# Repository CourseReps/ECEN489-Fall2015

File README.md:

# Data Acquisition &amp; Embedded Systems

## Description

The goal of this multidisciplinary project-based laboratory course is to provide instruction on data acquisition, system-level integration and design through a range of hands-on activities that complement the traditional classroom experience.
This includes circuit prototyping, PCB fabrication, microcontrollers and C++ programming, networking, and data visualization.
The main focus is on modular application development, algorithms, information management, control and actuation.
In addition, emphasis is put on team work, presentation skills, time management, creativity and innovation.

## Objectives

1. Enhance engineering education by facilitating learning through engineering projects.
2. Review the basics of circuit building, programming concepts, computer-aided design tools, the fundamentals of microcontrollers.
3. Foster leadership and team work, with division of labor, complementary tasks, discussion and integration.
4. Develop the ability to bridge theoretical concepts and practical tasks.
5. Master elements of experiential learning such as abstract conceptualization, active experimentation, concrete experience, reflective observation.
6. Improve transferable engineering skills and the ability to integrate different concepts.
7. Develop confidence and leadership.
8. Promote creativity and critical thinking.
9. Refine presentation skills and the ability to conduct and manage projects.

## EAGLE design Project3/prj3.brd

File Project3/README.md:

# Project 3

# Team Assignment

## [Team 1](https://github.com/CourseReps/ECEN489-Fall2015/wiki/project3-team1)

* Kartic Bhargav
* Thomas Branyon
* Henry Xiangdong Yu
* Kan Zheng

## [Team 2](https://github.com/CourseReps/ECEN489-Fall2015/wiki/project3-team2)

* Anthony Ramirez
* Keaton Brown
* Travis Taghavi
* Austin Taghavi
* Blade Roybal (Free Agent)

## [Team 3](https://github.com/CourseReps/ECEN489-Fall2015/wiki/project3-team3)

* Kaimen Walters
* Steven Jinpeng You
* Hai Li
* Pranay Eedara

## [Team 4](https://github.com/CourseReps/ECEN489-Fall2015/wiki/project3-team4)

* Udaya Bhaskar Kothapalli
* Abhay Anand
* Cooper Rehn
* Seungwon Yoon

# Simulation/Model Testing
In order to verify our models and algorithms, all the teams will test their models using the same values/input files.
##Problem 1
For the single-bucket volume estimation problem, we define the model to have the following parameters (equivalent to a standart 500ml beaker):
* Bucket diameter - 8cm
* Bucket height - 12cm
* Hole/leak diameter - 5mm
* Max flowrate - 3.5 L/min
    - Flowrate is assumed to be linear with PWM value between 0 and 255. i.e., PWM of 255 will yield a flowrate of 3.5L/min, and a PWM of 0 will yield a flow of 0L/min

Our input to the simulation will just be these four values, plus two more - a setpoint, and a height "jump" that occurs when the object is dropped in. To start, we will use the following test cases:
* Setpoint = 6cm, jump = 1cm
* Setpoint = 3cm, jump = 2cm

The input file will be all 6 values comma-separated. Example:

File 1:

    8, 12, 5, 3.5, 6, 1
    
File 2:

    8, 12, 5, 3.5, 3, 2

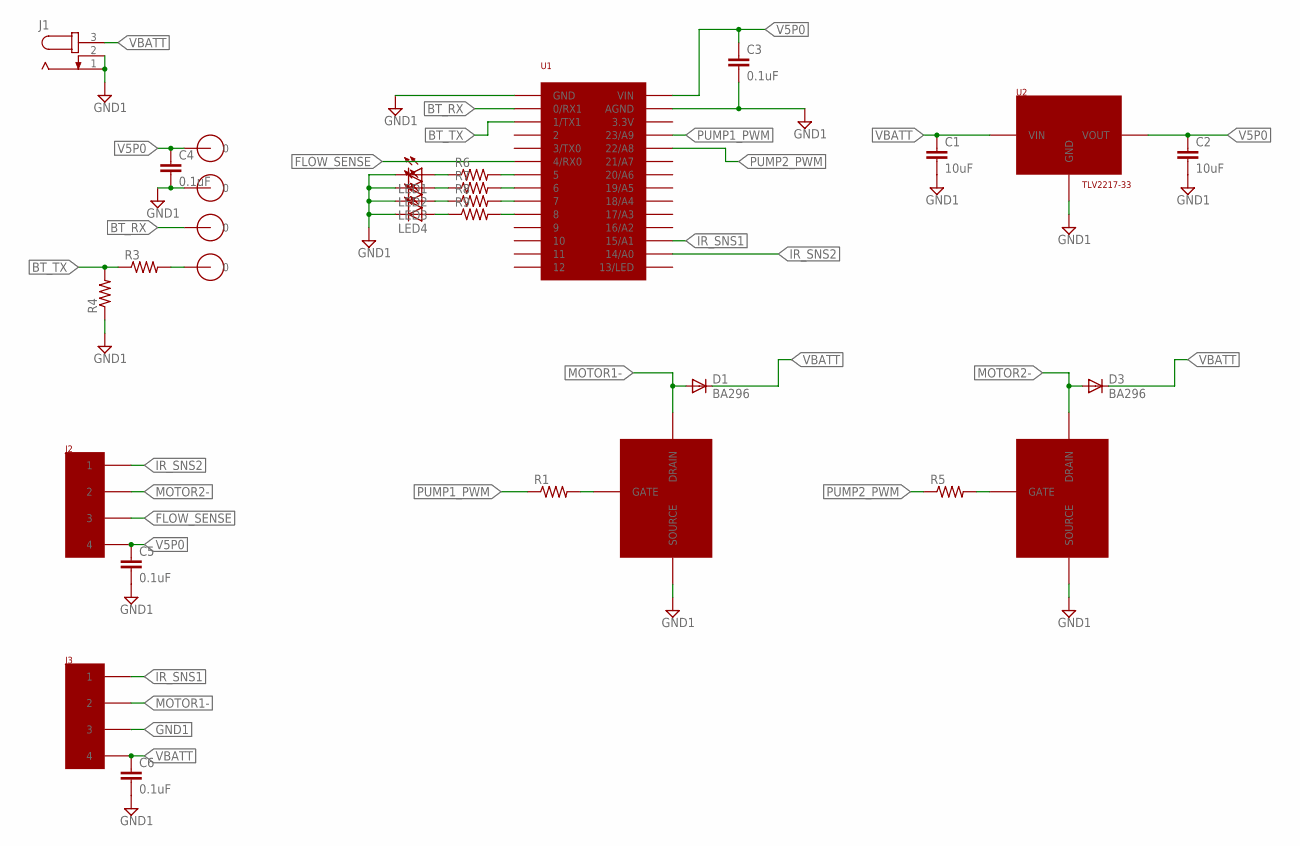
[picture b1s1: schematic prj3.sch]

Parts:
C1, C2: 10uF; C2.5-3
C3, C4, C5, C6: 0.1uF; C2.5-3
D1, D3: BA296; P2-15
J1: JACK-PLUG0; SPC4077
J2, J3: 1776119-4; 4P_SCREW_TERMINAL
J7, J8, J9, J10: 35MIL_HOLE
LED1, LED2, LED3, LED4: LED_ELD260; LED_LD260
R1, R3, R4, R5, R6, R7, R8, R9: R-US_0207/10; 0207/10
U1: TEENSY
U2: TLV2217-33; TO-220
U$2, U$3: NFET; TO-220

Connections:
BT_RX: J9.P$1, U1.P$2 (0/RX1)
BT_TX: R3.1, R4.2, U1.P$3 (1/TX1)
FLOW_SENSE: J2.P$3 (3), U1.P$6 (4/RX0)
GND1: C1.2, C2.2, C3.2, C4.2, C5.2, C6.2, J1.1, J1.2, J3.P$3 (3), J8.P$1, LED1.K (C), LED2.K (C), LED3.K (C), LED4.K (C), R4.1, U1.P$1 (GND), U1.P$32 (AGND), U2.2 (GND), U$2.3 (SOURCE), U$3.3 (SOURCE)
IR_SNS1: J3.P$1 (1), U1.P$22 (15/A1)
IR_SNS2: J2.P$1 (1), U1.P$21 (14/A0)
MOTOR1-: D1.A, J3.P$2 (2), U$2.2 (DRAIN)
MOTOR2-: D3.A, J2.P$2 (2), U$3.2 (DRAIN)
unnamed: R1.2, U$2.1 (GATE)
unnamed: R5.2, U$3.1 (GATE)
unnamed: R6.2, U1.P$7 (5)
unnamed: J10.P$1, R3.2
unnamed: R7.2, U1.P$8 (6)
unnamed: R8.2, U1.P$9 (7)
unnamed: R9.2, U1.P$10 (8)
unnamed: LED1.A, R6.1
unnamed: LED2.A, R7.1
unnamed: LED3.A, R8.1
unnamed: LED4.A, R9.1
PUMP1_PWM: R1.1, U1.P$30 (23/A9)
PUMP2_PWM: R5.1, U1.P$29 (22/A8)
V5P0: C2.1, C3.1, C4.1, C5.1, J2.P$4 (4), J7.P$1, U1.P$33 (VIN), U2.3 (VOUT)
VBATT: C1.1, C6.1, D1.C, D3.C, J1.3, J3.P$4 (4), U2.1 (VIN)

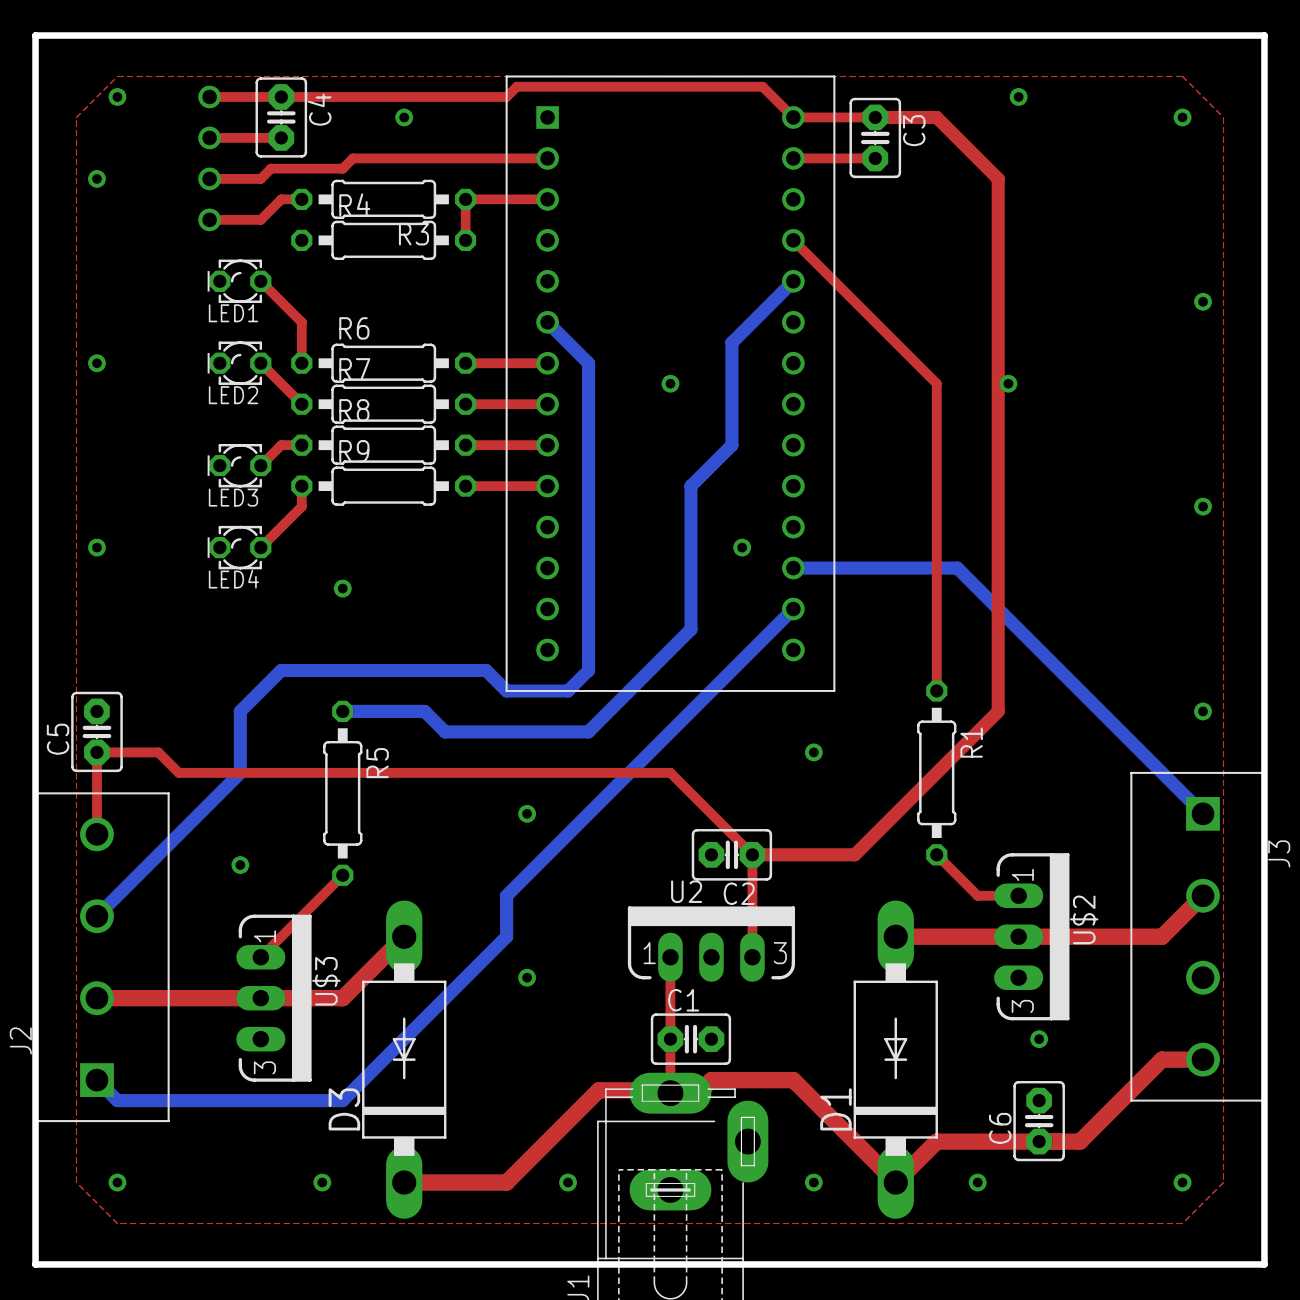
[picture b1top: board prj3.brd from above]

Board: 2 copper layers, 76.2 x 76.2 mm, 31 parts (0 on the bottom side), 23 nets.

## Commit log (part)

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2015-09-16 minor change
2015-09-16 Adding files for KiCad tutorial
2015-09-16 Adding Assignment 2 Programming Challenge
2015-09-16 Add optout3
2015-09-16 adding optout 3
2015-09-16 Adding Assignment 3
    Broken
2015-09-16 chaning port for server
2015-09-16 Updating Assignment 3
    Working now
2015-09-16 Added option to choose port in client
2015-09-16 Minor change to 3optout client
2015-09-16 Fixed format to ensure jpg rather than png
2015-09-16 Minor change in client
2015-09-16 cmake assignment3
2015-09-16 Deleting vestigial files.
2015-09-16 Assignment 4.
2015-09-17 Adding KiCad tutorial files
2015-09-17 Updating pictures
2015-09-17 3optout
2015-09-17 change name
2015-09-17 added tutorial folder :
2015-09-17 Updating 1optout
2015-09-18 Deleting .gitignore
2015-09-18 Adding 3optout
2015-09-18 Rename README to README.md
2015-09-18 Assignment 4
2015-09-18 cleanup
2015-09-18 optout3
2015-09-18 optout3 library files
2015-09-18 Rename arduinocode to arduinocode.ino
2015-09-18 optout3 readme files
2015-09-18 example of sqilte in c
2015-09-18 add the cmakelist
2015-09-20 assignment4
2015-09-20 4optout
2015-09-21 Adding server and client files
2015-09-21 Changing directory and adding CMakeLists
2015-09-21 Editing server so that it doesn't leave db open
2015-09-21 minor update
2015-09-21 Updating README.md
2015-09-21 final
2015-09-21 small deletions
2015-09-21 deleting unwanted files
2015-09-21 optout4 broadcast and server files
2015-09-21 Adding optout 4
2015-09-21 Adding port number as command line arg
2015-09-21 add optout4
2015-09-21 remove idea files
2015-09-21 Adding Assignment 4
2015-09-21 Assignment 5.
2015-09-22 Assignment 5
2015-09-23 update assignments
2015-09-23 Updating server.cpp
2015-09-24 assignment5
2015-09-24 add 4optout
2015-09-24 aaaa
2015-09-24 delete
2015-09-25 assn2 update
2015-09-25 optout4 updates
2015-09-25 Sample codes for Bluetooth tutorial
2015-09-25 Added assignment 5
2015-09-25 Adding Assignment 5 files
2015-09-25 no message
2015-09-25 Adding Assignment 5
2015-09-25 Updating Assignment 5
2015-09-25 asdf
2015-09-25 adding quickfire
2015-09-29 Adding readme
2015-09-29 Edited client.cpp
2015-09-29 assignment6
2015-09-30 Assignment 6
2015-09-30 initial commit of 6optout
2015-09-30 6optout
2015-09-30 Adding 6optout
2015-09-30 Editing README.md
2015-09-30 Adding 6optout files
2015-09-30 Add readme for 6optout
2015-09-30 added assignment 6
2015-09-30 Fixed Server.cpp bug
2015-09-30 optout6 files
2015-09-30 Changed to non-privileged port on client
2015-09-30 add optOut6
2015-09-30 Updated README for 6optout
2015-09-30 optout6 modification
2015-09-30 Adding Assignment 6
2015-09-30 update tutorials
2015-09-30 Assignment6 revision
2015-09-30 removing junk
2015-09-30 optout6 code update
2015-10-02 Corrected 6optout sources
2015-10-03 modify 6optout
2015-10-05 Fixed quickfire 3 files
2015-10-05 Adding Optout4
2015-10-05 test2foroptout7
2015-10-05 Adding quickfire and 7optout
2015-10-05 commiting 6optout and quickfire
2015-10-05 7optout
2015-10-05 Adding teams for Project 1.
2015-10-05 Adding graders.
2015-10-06 add 7optout
2015-10-06 Various updated files - merging
2015-10-06 Initial commit of 7optout - unstable
2015-10-06 Updated 7optout files
2015-10-07 Adding optout6
2015-10-07 optout6 edit teensy code
2015-10-07 optout7
2015-10-07 quickfire
2015-10-07 making a tiny change to ui
2015-10-07 Graders.
2015-10-07 Updating list of students in graders.cpp.
2015-10-07 optout7 threading
2015-10-08 optout7 threading update
2015-10-08 adding motor control tutorial sketch
2015-10-08 modified 7optout
2015-10-09 Adding client for Project1
2015-10-11 modify 7optout
2015-10-11 Adding PWM and Sensor Measurement
2015-10-12 small changes
2015-10-12 Updating client
2015-10-12 1project bluetoothbasic
2015-10-13 qtplot
2015-10-13 1project bluetooth server
2015-10-14 Adding Project1 Files
2015-10-14 Adding 7optout
2015-10-14 Adding project 1 sketch
2015-10-14 Project 1 code
2015-10-14 Adding arduino sensor reading code
2015-10-14 add project1
2015-10-14 plots for 1project
2015-10-14 Updating Proj 1
2015-10-15 Added new visualisation QT Creator project
2015-10-16 adding teensy code
2015-10-16 Adding Project1Server
2015-10-16 Final project 1 teensy sketch
2015-10-16 adding server
2015-10-16 updating server
2015-10-16 Project1 NUC code
2015-10-16 update server
2015-10-16 updating
2015-10-16 adding server and client and updating vis
2015-10-16 Updating Project1Server
2015-10-16 Updating visuals
2015-10-16 updating arduino code
2015-10-16 1project BTclient server working
2015-10-19 Adding teams for project 2.
2015-10-21 Add Schematic Project1
2015-10-21 Add CustomComponents
2015-10-23 adding arduino files for PID
2015-10-23 updating files
2015-10-23 adding proj2 temp sketch
2015-10-25 add project1 programs
2015-10-25 rm team2 directory in project1
2015-10-26 adding arduino PID code
2015-10-26 Adding Project2 folder
2015-10-28 Arduino code updated
2015-10-30 PID working code
2015-11-02 Adding proj 2 screenshots
2015-11-03 Adding teensy bluetooth prj2
2015-11-03 updating project 2 teensy sketch for BT
2015-11-04 2project Qt console
2015-11-04 2project Teensy code
2015-11-04 2project modified Qt
2015-11-04 2project teensy code updated
2015-11-04 Create project2
2015-11-04 updating plotter
2015-11-04 Adding server for P2
2015-11-04 modifying server
2015-11-04 updated arduino code
2015-11-04 project 2 files
2015-11-04 add images
2015-11-04 updated teensy sketch
2015-11-04 adding some debugging to server
2015-11-04 adding QT and Arduno
2015-11-06 Final Project 2
2015-11-06 deleting garbage
2015-11-06 adding board image
2015-11-06 updating server for bt reading
2015-11-06 add image
2015-11-09 solidworks
2015-11-09 Add Screenshots
2015-11-09 adding qt image
2015-11-13 File Clean up
2015-11-13 Project 3 schem
2015-11-13 pcb for project2
2015-11-13 Adding BOM
    v1
2015-11-13 Project 3 PCB
2015-11-15 Finished project 3 board and BOM
2015-11-16 Adding project 3 PCB files
2015-11-16 Add PCB Screenshot
2015-11-16 Moving project 3 PCB files to Team 4 folder
2015-11-16 Adding prelimiary Python code for the model
2015-11-16 add libraries used
2015-11-16 clean up folder
2015-11-16 Add PCB Screenshots
2015-11-16 arduino code for team4
2015-11-17 updates in 2project
2015-11-17 3project Qt model
2015-11-17 simulator demo
2015-11-18 modify simulator
2015-11-18 Adding Project3 Wiki images
2015-11-18 part1upload
2015-11-18 Update images in Project3
2015-11-18 update: adding label
2015-11-18 Adding PCB screens and block diagram
2015-11-18 3project image1
2015-11-18 singlt tank image
2015-11-18 remove image
2015-11-18 Adding project3 files
2015-11-18 Adding model stuff
2015-11-18 single tank image modified
2015-11-18 Adding images
2015-11-18 coupled tank image
2015-11-20 Adding images for project 3 wiki
2015-11-20 Adding Flow Rate calibration
    Measures flow rate from hall sensor and time taken to calibrate using a
    1L bottle. Updated constant can be used improve accuracy
2015-11-23 Update flowRate
    Updated to prevent max pump output at beginning
2015-11-23 Update flowRate
    Try 3
2015-11-30 modified for object volume calc
2015-11-30 Full model without visualization
2015-11-30 adding database
2015-11-30 update simulator
2015-11-30 committing database changes intermittantly, so that real time plotting is possible
2015-12-02 Project3 Server BT comms
2015-12-02 Adding ARduino code
2015-12-04 Updating proj 3 files
2015-12-04 updated project 3
2015-12-04 Adding teensy code (unstable). Base is Abhay Anand - Project 2.
2015-12-04 Adding pump cablibration routine
2015-12-06 Adding pictures for documentation
2015-12-06 fixing images
2015-12-06 add project 3
2015-12-07 modify project3
2015-12-07 Adding project 3 calibrations
2015-12-07 Adding newest teensy code. Object detection for tank 1 and comms for both tanks working. Volume calculation is off by a factor of 5-10.
2015-12-07 Adding PId code
2015-12-07 Adding PID2 code
2015-12-08 adding screenshot
2015-12-08 Committing working Project3-part1 code for Teensy
2015-12-08 proj3
2015-12-08 added photo
2015-12-09 proj3 pics
2015-12-09 Adding Project3 images
2015-12-09 adding calibration curves
2015-12-09 adding pix
2015-12-09 final modification for QT
2015-12-09 project3 team4 QT
2015-12-11 reorganizing project3 files and folders
2015-12-11 reorganizing proj3 of team4 files and folders
